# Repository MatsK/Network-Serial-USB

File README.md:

# Network-Serial-USB
USB Serial converter to use for configuring network devices such as Cisco, 3Com, HP and many more

## Goal

The goal is to create a PiggyBack module to a standard "CP2102 USB module" and to have two PiggyBack modules:

- Modular 8/8 connector aka RJ45 with a MAX232 to elevate the RS232 signals to standard levels.

- D-sub 9 connector with a MAX232 to elevate the RS232 signals to standard levels.

## Modification

The CP2102 USB module needs to be modified. The 90 angel pins needs to be desoldered and replaced with a 1x6 female pin header.

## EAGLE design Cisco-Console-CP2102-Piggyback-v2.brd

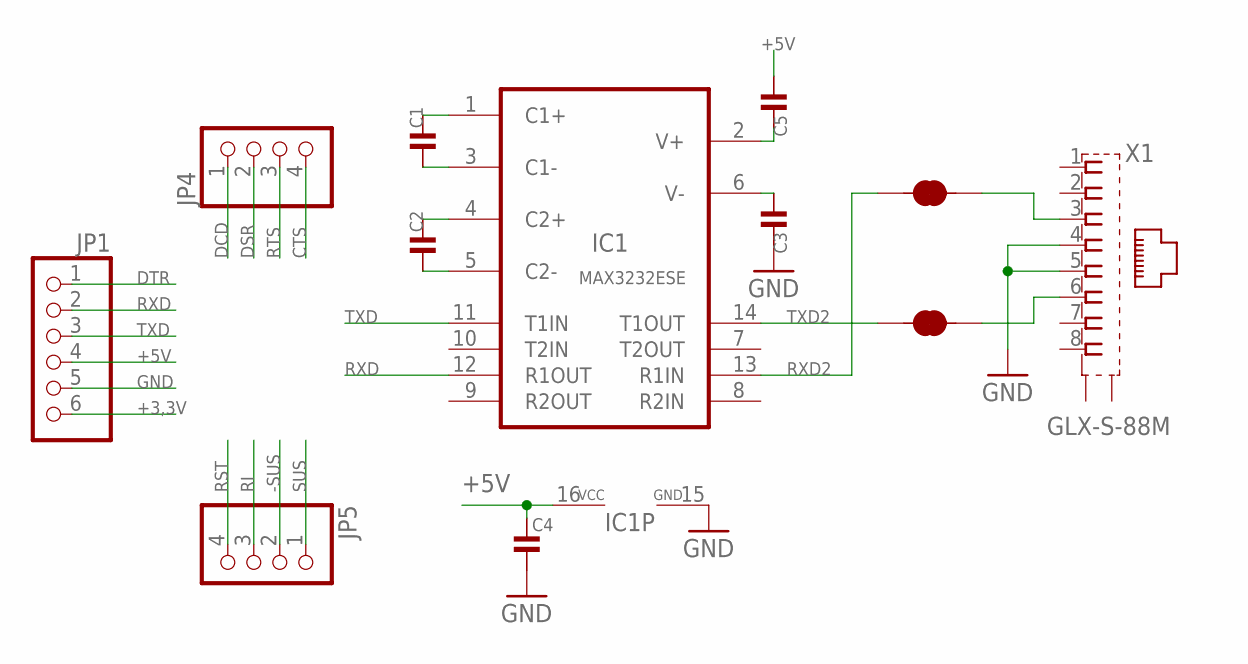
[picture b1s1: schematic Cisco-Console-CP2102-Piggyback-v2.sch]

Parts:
C1, C2, C3, C4, C5: MICROBUILDER_CAP_CERAMIC0402; MICROBUILDER_0402
IC1: MAX3232ESE; SO16
JP1: PINHD-1X6; 1X06
JP4, JP5: PINHD-1X4; 1X04
JP6, JP9: JUMPER-SMT_2_NC_TRACE_NO-SILK; SMT-JUMPER_2_NC_TRACE_NO-SILK
X1: GLX-S-88M

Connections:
+3,3V: JP1.6
+5V: C4.1, C5.1, IC1.16 (VCC), JP1.4
-SUS: JP5.2
CTS: JP4.4
DCD: JP4.1
DSR: JP4.2
DTR: JP1.1
GND: C3.2, C4.2, IC1.15 (GND), JP1.5, X1.4, X1.5
unnamed: C5.2, IC1.2 (V+)
unnamed: JP6.2, X1.3
unnamed: JP9.2, X1.6
unnamed: C3.1, IC1.6 (V-)
unnamed: C2.1, IC1.4 (C2+)
unnamed: C2.2, IC1.5 (C2-)
unnamed: C1.2, IC1.3 (C1-)
unnamed: C1.1, IC1.1 (C1+)
RI: JP5.3
RST: JP5.4
RTS: JP4.3
RXD: IC1.12 (R1OUT), JP1.2
RXD2: IC1.13 (R1IN), JP6.1
SUS: JP5.1
TXD: IC1.11 (T1IN), JP1.3
TXD2: IC1.14 (T1OUT), JP9.1

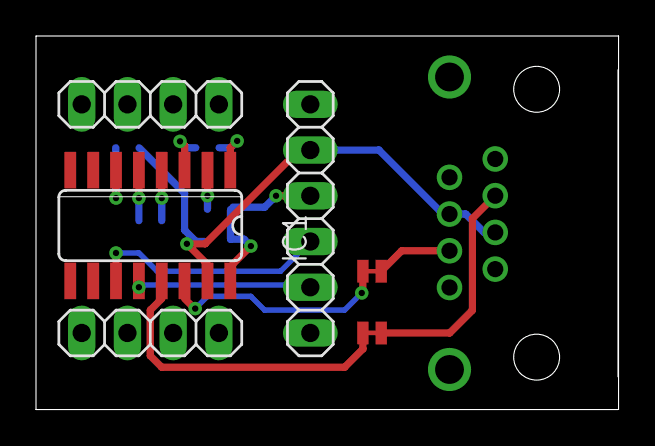
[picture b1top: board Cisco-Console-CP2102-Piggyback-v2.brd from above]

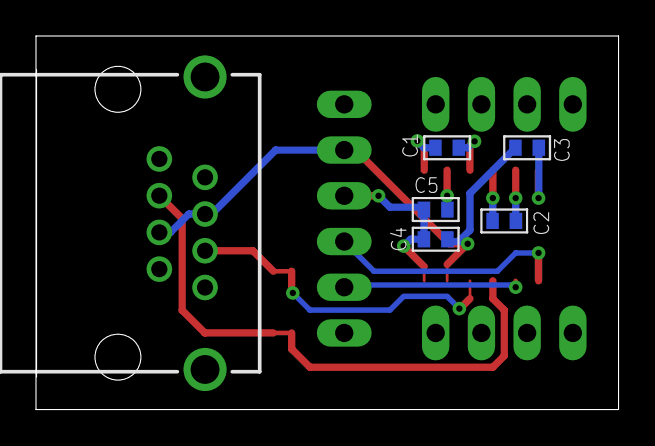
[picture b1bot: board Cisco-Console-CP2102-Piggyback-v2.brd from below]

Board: 2 copper layers, 32.4 x 20.8 mm, 12 parts (5 on the bottom side), 14 nets.

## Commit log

2019-11-09 First Pigyback commit
2019-11-09 Added text to README.md
2019-11-18 Added version 2 that has a more compact PCB
2019-11-18 Added top.png and bottom.png and added them to README.md
2019-11-18 Rotated top.png

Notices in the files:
parts and their libraries:
SparkFun-Jumpers: Licensing: Creative Commons ShareAlike 4.0 International - https://creativecommons.org/licenses/by-sa/4.0
